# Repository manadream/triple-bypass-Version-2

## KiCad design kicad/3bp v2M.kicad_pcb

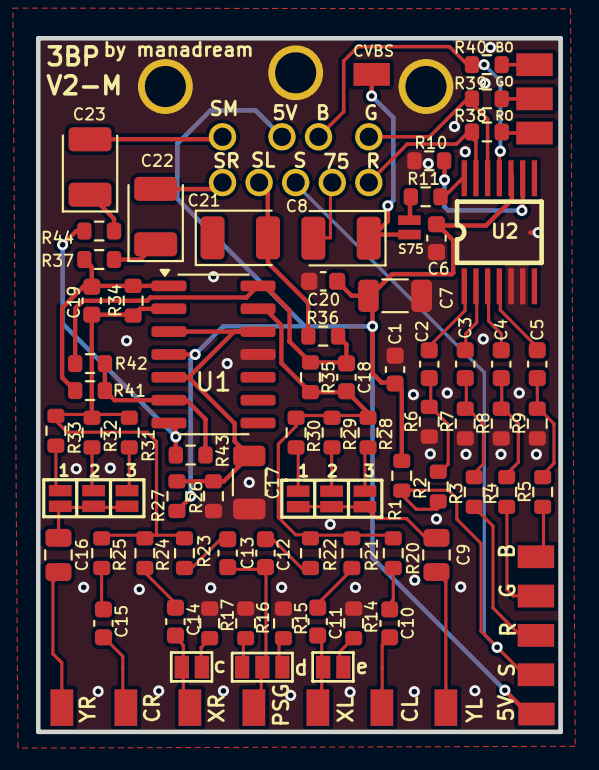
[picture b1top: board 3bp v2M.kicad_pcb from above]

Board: 2 copper layers, 29.0 x 38.5 mm, 84 parts (0 on the bottom side), 28 nets.

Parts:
1, 1#2: 3; JUMPER
5V1: TP_50; TP50
B1: TP_50; TP50
C1, C2, C3, C4, C5, C6, C20: 0.1uF/50V; C_0603_1608Metric
C7: 22uF/10V; C_1206_3216Metric
C8: 220uF/6.3V; CP_EIA-3528-15_AVX-H
C9, C16: 10uF/16V; C_0805_2012Metric
C10, C11, C12, C13, C14, C15: 1uF/16V; C_0603_1608Metric
C17: 10uF/16V; C_1206_3216Metric
C18, C19: 150pF/50V; C_0603_1608Metric
C21, C22, C23: 47uF/10V; CP_EIA-3528-15_AVX-H
CON1: MD-90SM
G: LOGO; OSHW-LOGO_5MM
G1: TP_50; TP50
R1, R15: 2.20k; R_0603_1608Metric
R2, R3, R4, R5: 5.62k; R_0603_1608Metric
R6, R7, R8, R9: 1k; R_0603_1608Metric
R10, R43: 4.7k; R_0603_1608Metric
R11, R14, R17: 75.0; R_0603_1608Metric
R16: 750; R_0603_1608Metric
R20, R21, R22, R23, R24, R25: 210k; R_0603_1608Metric
R26, R27, R30, R33, R41, R42: 10k; R_0603_1608Metric
R28, R31: 130k; R_0603_1608Metric
R29, R32: 100k; R_0603_1608Metric
R34, R35: 300k; R_0603_1608Metric
R36, R37, R44: 330; R_0603_1608Metric
R38, R39, R40: 511; R_0603_1608Metric
RIN: TP_50; TP50
S1: TP_50; TP50
SL1: TP_50; TP50
SN1: TP_50; TP50
SR2: TP_50; TP50
U1: TL974IDR; SOIC-14_3.9x8.7mm_P1.27mm
U2: THS7374IPWR; TSSOP-14
XL1: TP_50; TP50
XR2: TP_50; TP50
YL1: TP_50; TP50
YR2: TP_50; TP50
c: JUMPER_PADSX2
d: JUMPER_PADSX3
e: JUMPER_PADSX2

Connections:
32X-LEFT: C11.1, C11.2, R14.1, R21.1, SL1.1, e.1, e.2
32X-RIGHT: C14.1, C14.2, R17.1, R24.1, XR2.1, c.1, c.2
+5V: 5V1.1, C1.1, C6.1, C7.1, C20.1, CON1.2, R1.2, R27.1, U1.4, U2.10
B-IN: B1.1, C5.1, C5.2, R5.1, R5.2, R9.2, U2.4
B-OUT: CON1.1, R40.1, R40.2, U2.11
G-IN: C4.1, C4.2, G1.1, R4.1, R4.2, R8.2, U2.3
G-OUT: CON1.3, R39.1, R39.2, U2.12
GND: C1.2, C6.2, C7.2, C17.2, C20.2, CON1.10, R6.1, R7.1, R8.1, R9.1, R10.1, R14.2, R15.2, R16.2, R17.2, R26.1, U1.11, U2.5, U2.6
LEFT: C18.2, R20.2, R21.2, R22.2, R28.2, R29.2, R30.2, R35.2, U1.13
LOUT: C18.1, R35.1, R36.2, R42.2, U1.14
LPF: R10.2, U2.9
MONO: R41.1, R42.1, R43.1, U1.6
MOUT: R43.2, R44.1, U1.7
OPAVREF: C17.1, R26.2, R27.2, U1.3, U1.5, U1.12
PSG: C12.1, C12.2, C13.1, C13.2, R15.1, R16.1, R22.1, R23.1, SN1.1, d.1, d.2, d.3
R-IN: C3.1, C3.2, R3.1, R3.2, R7.2, RIN.1, U2.2
R-OUT: CON1.7, R38.1, R38.2, U2.13
RIGHT: C19.1, R23.2, R24.2, R25.2, R31.2, R32.2, R33.2, R34.1, U1.2
ROUT: C19.2, R34.2, R37.1, R41.2, U1.1
SCD-LEFT: C10.1, C10.2, R20.1, XL1.1
SCD-RIGHT: C15.1, C15.2, R25.1, SR2.1
SL: C21.1, C21.2, CON1.8, R36.1
SM: C23.1, C23.2, CON1.6, R44.2
SR: C22.1, C22.2, CON1.9, R37.2
SYNC-75: C8.1, C8.2, CON1.4, R11.1
SYNC-OUT: C2.1, C2.2, CON1.5, R1.1, R2.1, R2.2, R6.2, R11.2, S1.1, U2.1, U2.14
YM-LEFT: 1.1, 1.2, C9.1, C9.2, R28.1, R29.1, R30.1, YL1.1
YM-RIGHT: 1#2.1, 1#2.2, C16.1, C16.2, R31.1, R32.1, R33.1, YR2.1

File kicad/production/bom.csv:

Designator,Footprint,Quantity,Value,LCSC Part #
"C1, C2, C20, C3, C4, C5, C6",0603,7,0.1uF/50V,
"C10, C11, C12, C13, C14, C15",0603,6,1uF/16V,
"C16, C9",0805,2,10uF/16V,
C17,1206,1,10uF/16V,
"C18, C19",0603,2,150pF/50V,
"C21, C22, C23",CP_EIA-3528-15_AVX-H,3,47uF/10V,
C7,1206,1,22uF/10V,
C8,CP_EIA-3528-15_AVX-H,1,220uF/6.3V,
"R1, R15",0603,2,2.20k,
"R10, R43",0603,2,4.7k,
"R11, R14, R17",0603,3,75.0,
R16,0603,1,750,
"R2, R3, R4, R5",0603,4,5.62k,
"R20, R21, R22, R23, R24, R25",0603,6,210k,
"R26, R27, R30, R33, R41, R42",0603,6,10k,
"R28, R31",0603,2,130k,
"R29, R32",0603,2,100k,
"R34, R35",0603,2,300k,
"R36, R37, R44",0603,3,330,
"R38, R39, R40",0603,3,511,
"R6, R7, R8, R9",0603,4,1k,
U1,SOIC-14_3.9x8.7mm_P1.27mm,1,TL974IDR,
U2,TSSOP-14,1,THS7374IPWR,

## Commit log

2022-03-04 SL and SL were labeled backwards. fixed.
2022-05-17 Fixed description
2025-05-29 added my modifications
2025-06-27 Added 4 channel op amp to restore mono and cleaned up repo

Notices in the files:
kicad/3bp v2M.kicad_pcb:
Licensed under CERN OHL v.1.2
